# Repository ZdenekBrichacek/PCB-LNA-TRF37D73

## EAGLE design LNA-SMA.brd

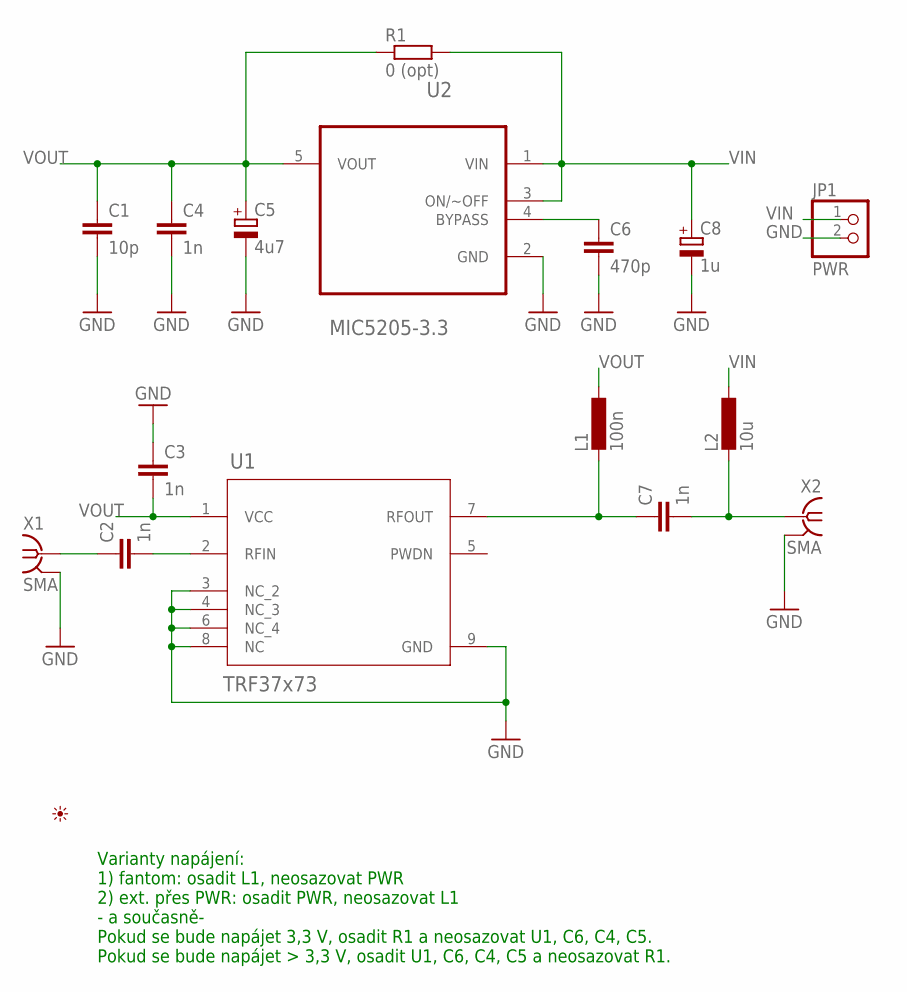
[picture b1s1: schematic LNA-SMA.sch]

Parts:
C1: 10p; C0603
C2, C3, C4, C7: 1n; C0603
C5: 4u7; SMC_A
C6: 470p; C0603
C8: 1u; SMC_A
JP1: PWR; 1X02
L1: 100n; L2012C
L2: 10u; L2012C
R1: 0 (opt); R0603
U1: TRF37x73; DSG0008A
U2: MIC5205-3.3; SOT95P280X145-5N
U$1: PICTO_1
X1, X2: SMA; J502-ND-142-0701-801/806

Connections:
GND: C1.2, C3.1, C4.2, C5.-, C6.2, C8.-, JP1.2, U1.3 (NC_2), U1.4 (NC_3), U1.6 (NC_4), U1.8 (NC), U1.9 (GND), U2.2 (GND), X1.G@1 (2), X1.G@2 (2), X1.G@3 (2), X1.G@4 (2), X2.G@1 (2), X2.G@2 (2), X2.G@3 (2), X2.G@4 (2)
unnamed: C6.1, U2.4 (BYPASS)
unnamed: C2.2, U1.2 (RFIN)
unnamed: C7.1, L1.2, U1.7 (RFOUT)
RF_IN: C7.2, L2.2, X2.1
RF_OUT: C2.1, X1.1
VIN: C8.+, JP1.1, L2.1, R1.2, U2.1 (VIN), U2.3 (ON/~OFF)
VOUT: C1.1, C3.2, C4.1, C5.+, L1.1, R1.1, U1.1 (VCC), U2.5 (VOUT)

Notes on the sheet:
Varianty napájení: 1) fantom: osadit L1, neosazovat PWR 2) ext. přes PWR: osadit PWR, neosazovat L1 - a současně- Pokud se bude napájet 3,3 V, osadit R1 a neosazovat U1, C6, C4, C5. Pokud se bude napájet > 3,3 V, osadit U1, C6, C4, C5 a neosazovat R1.

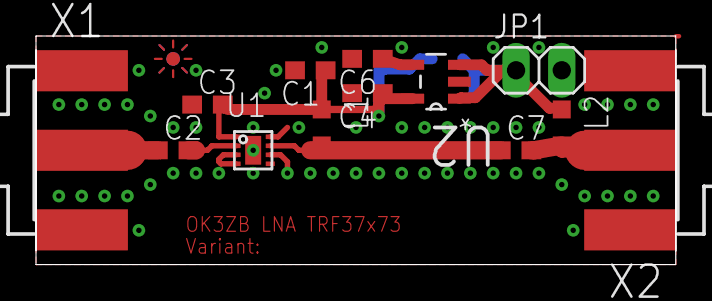
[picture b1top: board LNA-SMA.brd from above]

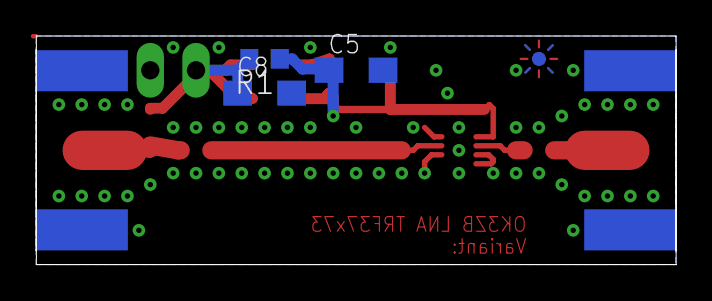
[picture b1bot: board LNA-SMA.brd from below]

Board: 2 copper layers, 35.6 x 12.7 mm, 17 parts (3 on the bottom side), 8 nets.

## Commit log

2017-10-10 :space_invader: Added .gitattributes & .gitignore files
2017-10-10 Initial version
